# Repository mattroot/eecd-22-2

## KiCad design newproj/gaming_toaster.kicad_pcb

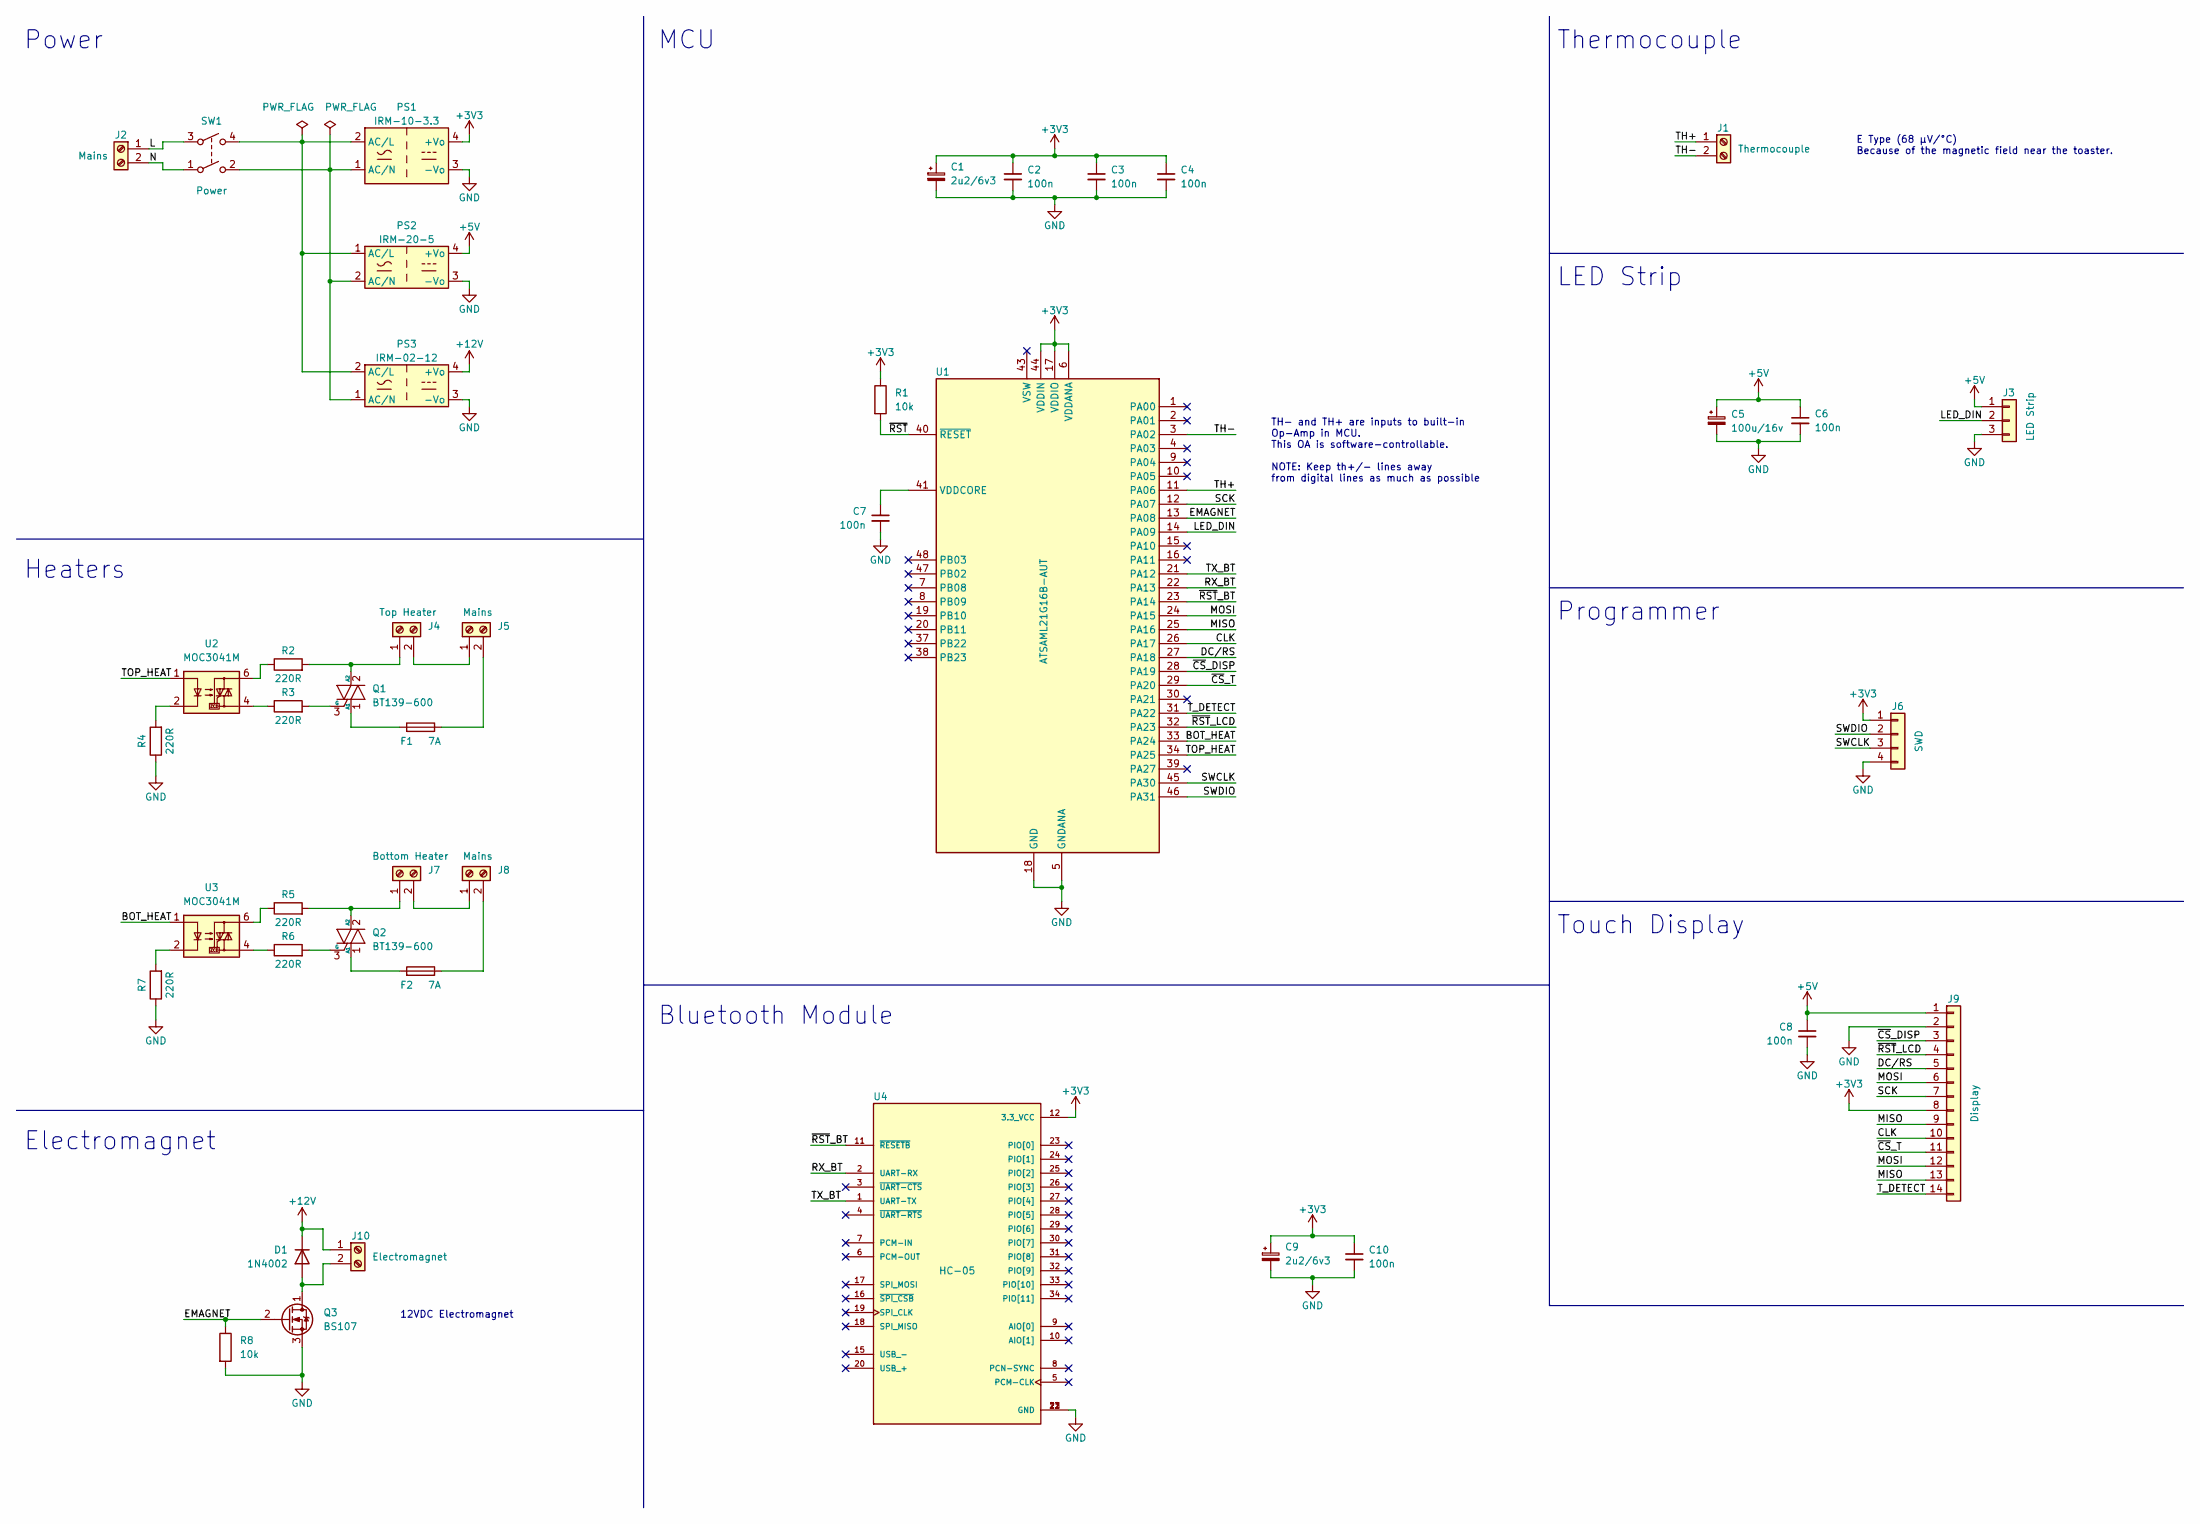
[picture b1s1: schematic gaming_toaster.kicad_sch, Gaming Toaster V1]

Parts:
C1, C9: 2u2/6v3; CP_Elec_4x3
C2, C3, C4, C6, C7, C8, C10: 100n; C_0603_1608Metric
C5: 100u/16v; CP_Elec_6.3x3.9
D1: 1N4002; D_SMA
F1, F2: 7A; Fuseholder_Clip-5x20mm_Littelfuse_520_Inline_P20.50x5.80mm_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
J1: Thermocouple; Molex_Micro-Fit_3.0_43650-0215_1x02_P3.00mm_Vertical
J2, J5, J8: Mains; TerminalBlock_bornier-2_P5.08mm
J3: LED Strip; Molex_Micro-Fit_3.0_43650-0315_1x03_P3.00mm_Vertical
J4: Top Heater; TerminalBlock_bornier-2_P5.08mm
J6: SWD; PinHeader_1x04_P2.54mm_Vertical
J7: Bottom Heater; TerminalBlock_bornier-2_P5.08mm
J9: Display; Molex_SlimStack_502426-1410_2x07_P0.40mm_Vertical
J10: Electromagnet; TerminalBlock_bornier-2_P5.08mm
PS1: IRM-10-3.3; Converter_ACDC_MeanWell_IRM-10-xx_THT
PS2: IRM-20-5; Converter_ACDC_MeanWell_IRM-20-xx_THT
PS3: IRM-02-12; Converter_ACDC_MeanWell_IRM-02-xx_THT
Q1, Q2: BT139-600; TO-220-3_Vertical
Q3: BS107; TO-92_Inline
R1, R8: 10k; R_0603_1608Metric
R2, R3, R4, R5, R6, R7: 220R; R_0603_1608Metric
SW1: Power; SolderWire-0.75sqmm_1x04_P4.8mm_D1.25mm_OD2.3mm
U1: ATSAML21G16B-AUT; TQFP-48_7x7mm_P0.5mm
U2, U3: MOC3041M; DIP-6_W7.62mm
U4: HC-05; PARTREV v1.0

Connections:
+3V3: C1.1, C2.1, C3.1, C4.1, C9.1, C10.1, J6.1, J9.8, PS1.4 (+Vo), R1.1, U1.6 (VDDANA), U1.17 (VDDIO), U1.36 (VDDIO), U1.44 (VDDIN), U4.12 (3.3_VCC)
+5V: C5.1, C6.1, C8.1, J3.1, J9.1, PS2.4 (+Vo)
+12V: D1.1 (K), J10.1, PS3.4 (+Vo)
/BOT_HEAT: U1.33 (PA24), U3.1
/CLK: J9.10, U1.26 (PA17)
/DC/RS: J9.5, U1.27 (PA18)
/EMAGNET: Q3.2 (G), R8.1, U1.13 (PA08)
/L: J2.1, SW1.3
/LED_DIN: J3.2, U1.14 (PA09)
/MISO: J9.9, J9.13, U1.25 (PA16)
/MOSI: J9.6, J9.12, U1.24 (PA15)
/N: J2.2, SW1.1
/RX_BT: U1.22 (PA13), U4.2 (UART-RX)
/SCK: J9.7, U1.12 (PA07)
/SWCLK: J6.3, U1.45 (PA30)
/SWDIO: J6.2, U1.46 (PA31)
/TH+: J1.1, U1.11 (PA06)
/TH-: J1.2, U1.3 (PA02)
/TOP_HEAT: U1.34 (PA25), U2.1
/TX_BT: U1.21 (PA12), U4.1 (UART-TX)
/T_DETECT: J9.14, U1.31 (PA22)
/~CS_DISP: J9.3, U1.28 (PA19)
/~CS_T: J9.11, U1.29 (PA20)
/~RST: R1.2, U1.40 (~RESET)
/~RST_BT: U1.23 (PA14), U4.11 (~RESETB)
/~RST_LCD: J9.4, U1.32 (PA23)
GND: C1.2, C2.2, C3.2, C4.2, C5.2, C6.2, C7.2, C8.2, C9.2, C10.2, J3.3, J6.4, J9.2, PS1.3 (-Vo), PS2.3 (-Vo), PS3.3 (-Vo), Q3.3 (S), R4.1, R7.1, R8.2, U1.5 (GNDANA), U1.18 (GND), U1.35 (GND), U1.42 (GND), U4.13 (GND), U4.21 (GND), U4.22 (GND)
unnamed: PS1.2 (AC/L), PS2.1 (AC/L), PS3.2 (AC/L), SW1.4
unnamed: PS1.1 (AC/N), PS2.2 (AC/N), PS3.1 (AC/N), SW1.2
unnamed: D1.2 (A), J10.2, Q3.1 (D)
unnamed: J4.1, Q1.2 (A2), R2.2
unnamed: J4.2, J5.1
unnamed: F1.1, J5.2
unnamed: J7.1, Q2.2 (A2), R5.2
unnamed: J7.2, J8.1
unnamed: F2.1, J8.2
unnamed: F1.2, Q1.1 (A1)
unnamed: Q1.3 (G), R3.2
unnamed: F2.2, Q2.1 (A1)
unnamed: Q2.3 (G), R6.2
unnamed: R2.1, U2.6
unnamed: R3.1, U2.4
unnamed: R4.2, U2.2
unnamed: R5.1, U3.6
unnamed: R6.1, U3.4
unnamed: R7.2, U3.2
unnamed: C7.1, U1.41 (VDDCORE)

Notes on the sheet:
MCU
Power
Bluetooth Module
E Type (68 µV/°C) Because of the magnetic field near the toaster.
Touch Display
Heaters
12VDC Electromagnet
LED Strip
Electromagnet
Thermocouple
TH- and TH+ are inputs to built-in Op-Amp in MCU. This OA is software-controllable. NOTE: Keep th+/- lines away from digital lines as much as possible
Programmer

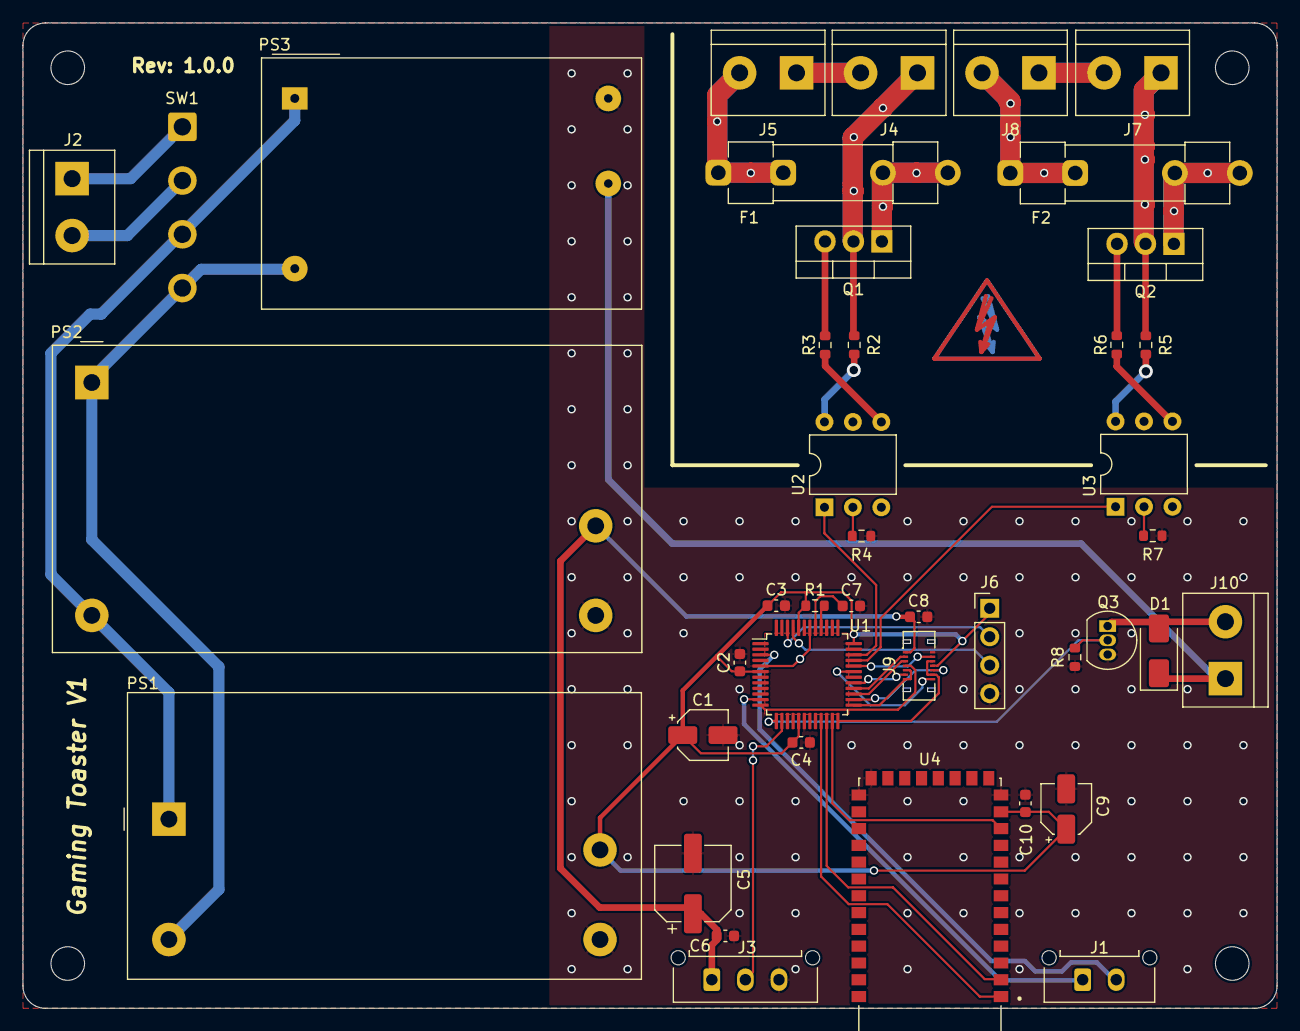
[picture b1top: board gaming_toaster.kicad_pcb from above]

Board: 2 copper layers, 112.0 x 88.0 mm, 42 parts (0 on the bottom side), 47 nets.

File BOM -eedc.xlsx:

# | Element | Q-ty | buying price | buying price | Shop
1 | 4DLCD-24320240-CTP-IPS4D SYSTEMS | 1 | 25.45 [USD/SZT] | 25.45 [USD/50 SZT] | https://www.tme.eu/en/details/4dlcd-24320240-ci/lcd-graphic-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
2 | ESP32­S3­WROOM­2 | 1 | 46.06 [USD/SZT] | 46.06 [USD/50 SZT] | https://www.tme.eu/pl/details/esp32s3-wrm2-16r8v/moduly-iot-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
3 | KAM1505CHINFA ELECTRONICS AC-DC 5v | 1 | 26.5 [USD/SZT] | 26.5 [USD/50 SZT] | https://www.tme.eu/pl/details/ac15w85-265_5/przetwornice-ac-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
4 | AME1-3.3SJZAIMTEC AC-DC 3.3v | 1 | 10.91 [USD/SZT] | 10.91 [USD/50 SZT] | https://www.tme.eu/pl/details/ame1-3.3sjz/przetwornice-ac-dc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
5 | KAM1503 AC - DC POWER MODULE13 ~ 15W UL / cUL / TUV / CE | 1 | 1.8 [USD/SZT] | 1.8 [USD/50 SZT] | https://www.compel.ru/infosheet/CHINFA/KAM1503
6 | ZIF0540DH-CF25RIVERDI | 1 | 1.6 [USD/SZT] | 1.6 [USD/50 SZT] | https://www.tme.eu/en/details/zif0540dh-cf25/displays-access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
7 | WS2812BWORLDSEMI | 1 | 0.4 [USD/SZT] | 0.4 [USD/50 SZT] | https://www.tme.eu/pl/details/ws2812b/diody-led-smd-kolorowe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
8 | H8553VBBG3076WBULGIN | 1 | 4.51 [USD/SZT] | 4.51 [USD/50 SZT] | https://www.tme.eu/pl/details/ae-h8553vbnac/przelaczniki-typ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
9
10 | IRM-20-5 - Mean Well Web | 1 | 12.27 [USD/SZT] | 11.98 [USD/50 SZT] | https://www.meanwell-web.com/en-gb/ac-dc-single-output-encap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
11 | Kondensator elektrolityczny SMD 10UF 16V | 3 | 0.09 [USD/SZT] | 0.03 [USD/50 SZT] | https://www.trim-pot.com.pl/pl/p/Kondensator-elektrolityczny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
12 | Philips Cc 2U2 6V3 | 6 | 0.38 [USD/SZT] | 0.26 [USD/50 SZT] | https://nowyelektronik.pl/index.php?id_product=28116&control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
13 | ATSAML21G16B-AUT | 1 | 4.43 [USD/SZT] | 3.98 [USD/50 SZT] | https://www.mouser.pl/ProductDetail/Microchip-Technology/ATS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
14 | PinHeader 1x04 P 2.54mm_Vertical | 1 | 0.87 [USD/SZT] | 0.59 [USD/50 SZT] | https://www.mouser.pl/ProductDetail/Mill-Max/310-47-105-41-0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
15 | R_0603_1608 Metric 220R | 6 | 3.00 [USD/SZT] | 2.14 [USD/50 SZT] | https://www.mouser.pl/c/passive-components/resistors/smd-res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
16 | R_0603_1608 Metric 100n | 9 | 3.00 [USD/SZT] | 2.14 [USD/50 SZT] | https://www.mouser.pl/c/passive-components/resistors/smd-res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
17 | 691214110002S | 1 | 1.20 [USD/SZT] | 1.10 [USD/50 SZT] | https://www.mouser.pl/ProductDetail/Wurth-Elektronik/6912141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
18 | PTS645SL50-2 LFSC&K | 1 | 0.23 [USD/SZT] | 0.19[USD/50 SZT] | https://www.tme.eu/pl/details/pts645sl50-2/mikroprzelaczniki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
19 | MOC3041M | 2 | 1.11 [USD/SZT] | 0.48[USD/50 SZT] | https://www.mouser.pl/ProductDetail/onsemi-Fairchild/MOC3041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
20 | Littelfuse 05200001N | 2 | 0.30 [USD/SZT] | 0.27[USD/50 SZT] | https://us.rs-online.com/product/littelfuse/05200001n/70519399/
21 | BS107 MOS-N-FET 200V 0.15A 0.8W TO92 | 1 | 0.65 [USD/SZT] | 0.58[USD/50 SZT] | https://www.sklep.cyfronika.com.pl/pl/p/BS107-Tranzystor-MOS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
22 | BLUETOOTH HC-05 AVR ARM ARDUINO | 1 | 6.33 [USD/SZT] | 6.11[USD/50 SZT] | https://modulosy.pl/moduly-radiowe/105-modul-bluetooth-hc-05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
23 | PWR-SWITCH 230V 16A | 1 | 8.13 [USD/SZT] | 7.82[USD/50 SZT] | https://www.olimex.com/Products/Duino/Shields/PWR-SWITCH/
24 | MAX6675 Thermocouple | 1 | 5.86 [USD/SZT] | 5.62[USD/50 SZT] | https://sklep.avt.pl/modul-max6675-miernik-temperatury-do-te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
25 | R_0603_1608 Metric 10k | 2 | 3.00 [USD/SZT] | 2.14 [USD/50 SZT] | https://www.mouser.pl/c/passive-components/resistors/smd-res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
26 | BT139-600E 600V/16A - THT - 5szt. | 2 | 3.31 [USD/SZT] | 3.14 [USD/50 SZT] | https://botland.com.pl/triaki/1280-triak-bt139-600e-600v16a-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
27 | 1776275-2TE CONNECTIVITY | 1 | 0.52 [USD/SZT] | 0.43 [USD/50 SZT] | https://www.tme.eu/pl/details/1776275-2/listwy-zaciskowe-do-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
28 | 436450200 MOLEX | 1 | 0.92 [USD/SZT] | 0.37 [USD/50 SZT] | https://www.tme.eu/pl/details/mx-43645-0200/zlacza-sygnalowe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
29 | M20-7820446 | 1 | 1.03 [USD/SZT] | 0.83 [USD/50 SZT] | https://www.mouser.pl/ProductDetail/Harwin/M20-7820446?qs=vF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
30 | Terminal block Connector 2pin | 1 | 0.58 [USD/SZT] | 0.47 [USD/50 SZT] | https://eshop.sectron.pl/pl/terminal-block-connector-2pin/p-1404/
31 | IRM-02-12 MEAN WELL | 1 | 7.01 [USD/SZT] | 6.15 [USD/50 SZT] | https://www.tme.eu/pl/details/irm-02-12/zasilacze-do-wbudowa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
32 | 1N4002-DIODES | 1 | 0.17 [USD/SZT] | 0.11 [USD/50 SZT] | https://www.mouser.pl/ProductDetail/Diodes-Incorporated/1N40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
33 | 1776275-2TE CONNECTIVITY | 1 | 0.52 [USD/SZT] | 0.43 [USD/50 SZT] | https://www.tme.eu/pl/details/1776275-2/listwy-zaciskowe-do-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
34 | 709-IRM10-3.3 MEAN WELL | 1 | 11.12 [USD/SZT] | 10.12 [USD/50 SZT] | https://www.mouser.pl/ProductDetail/MEAN-WELL/IRM-10-3.3?qs=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

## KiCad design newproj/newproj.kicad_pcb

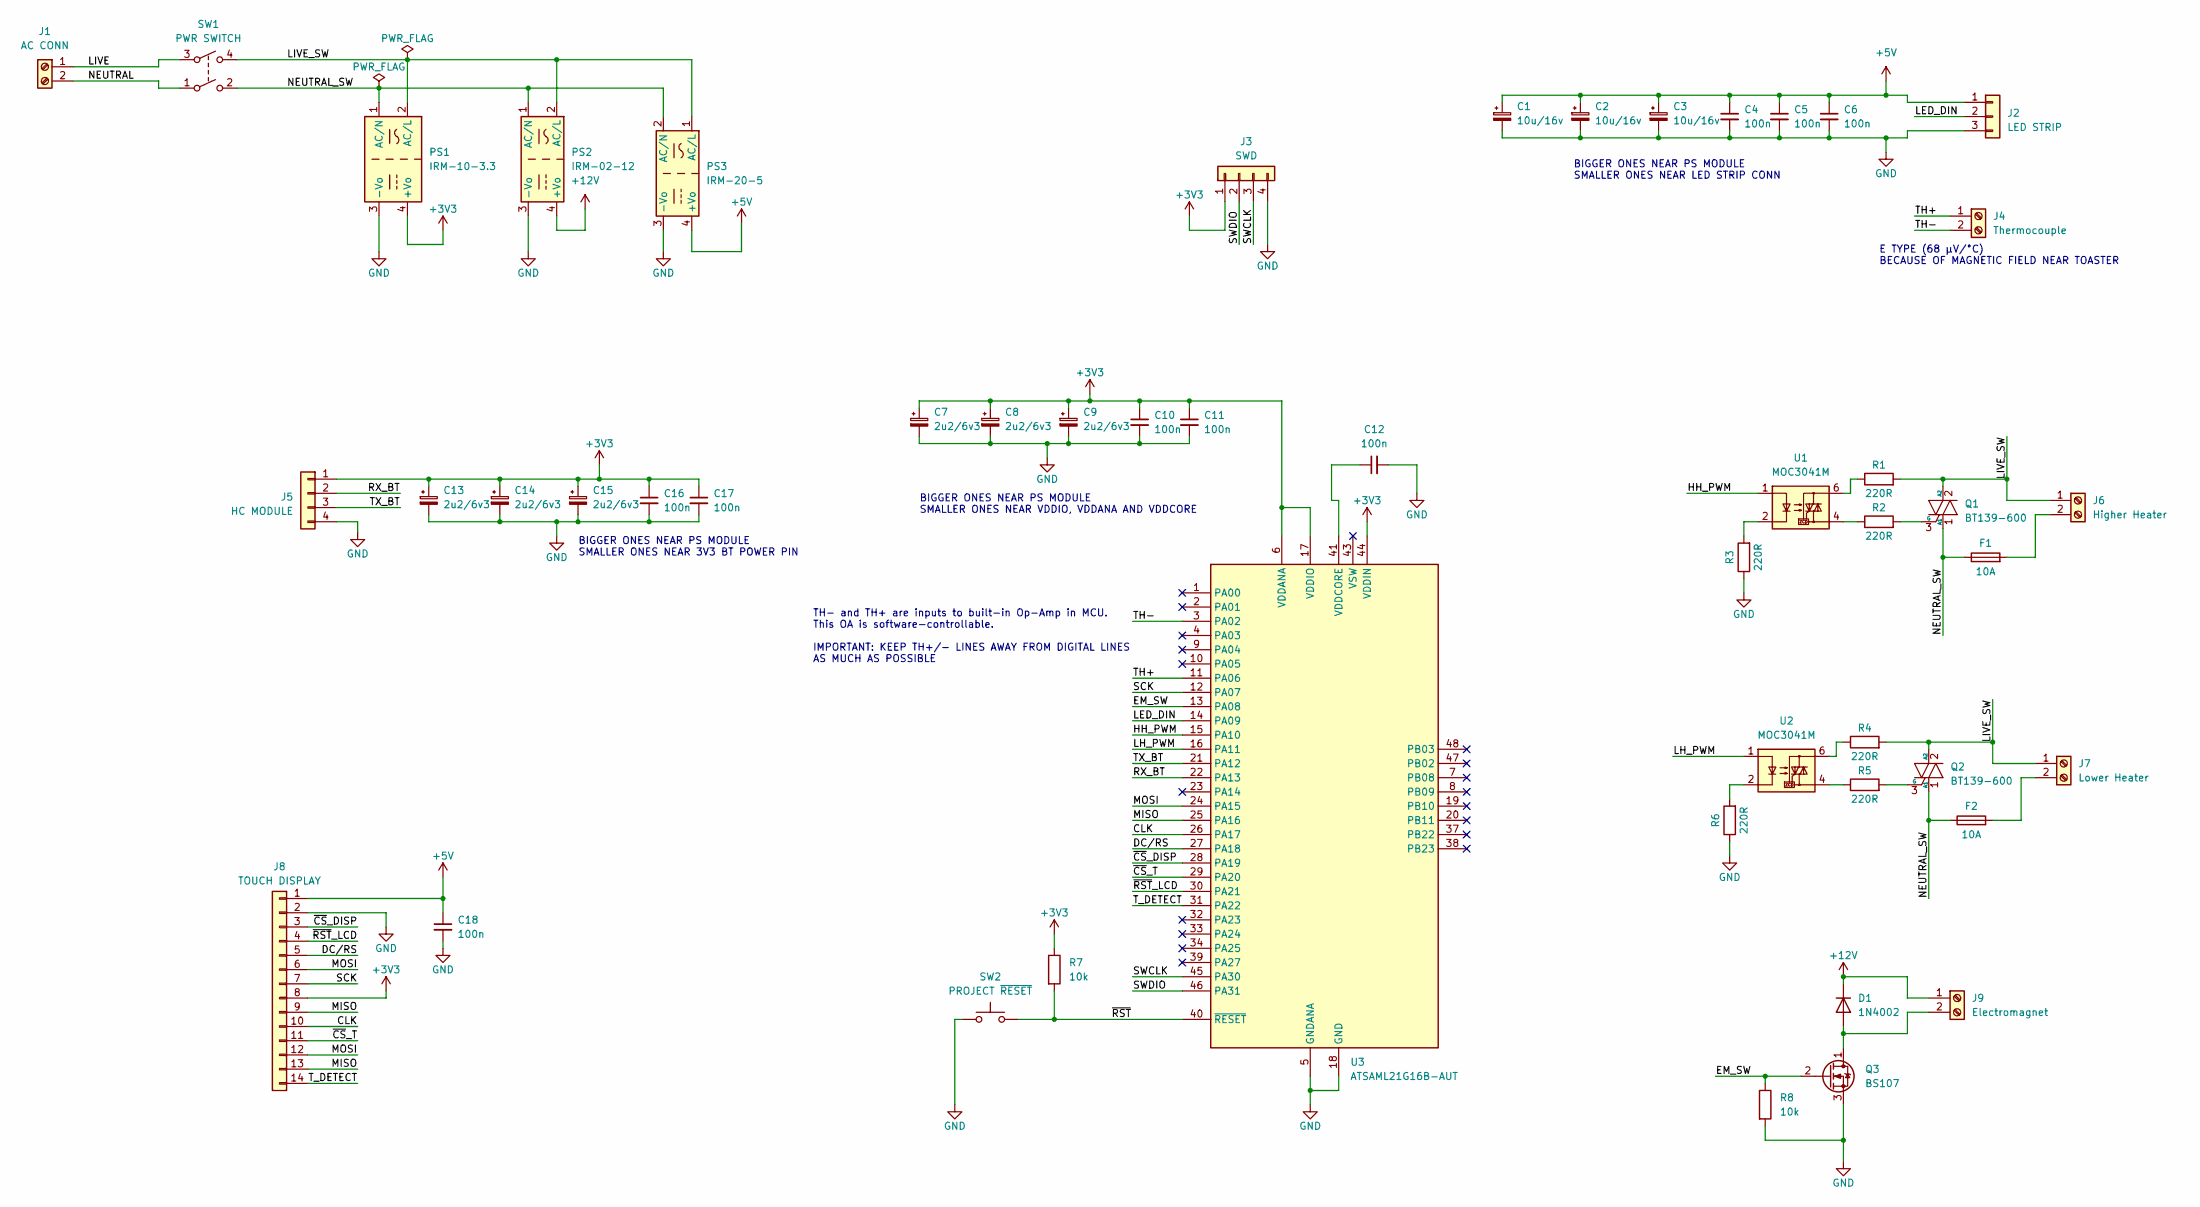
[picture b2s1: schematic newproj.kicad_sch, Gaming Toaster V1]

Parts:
C1, C2, C3: 10u/16v; CP_Elec_6.3x3.9
C4, C5, C6, C10, C11, C12, C16, C17, C18: 100n; C_0603_1608Metric
C7, C8, C9, C13, C14, C15: 2u2/6v3; CP_Elec_4x3
D1: 1N4002; D_SMA
F1, F2: 10A; Fuseholder_Clip-5x20mm_Littelfuse_520_Inline_P20.50x5.80mm_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
J1: AC CONN; TerminalBlock_bornier-2_P5.08mm
J2: LED STRIP; Molex_Micro-Fit_3.0_43650-0315_1x03_P3.00mm_Vertical
J3: SWD; PinHeader_1x04_P2.54mm_Vertical
J4: Thermocouple; TerminalBlock_bornier-2_P5.08mm
J5: HC MODULE; PinHeader_1x04_P2.54mm_Vertical
J6: Higher Heater; TerminalBlock_bornier-2_P5.08mm
J7: Lower Heater; TerminalBlock_bornier-2_P5.08mm
J8: TOUCH DISPLAY; PinHeader_1x14_P2.54mm_Vertical
J9: Electromagnet; TerminalBlock_bornier-2_P5.08mm
PS1: IRM-10-3.3; Converter_ACDC_MeanWell_IRM-10-xx_THT
PS2: IRM-02-12; Converter_ACDC_MeanWell_IRM-02-xx_THT
PS3: IRM-20-5; Converter_ACDC_MeanWell_IRM-20-xx_THT
Q1, Q2: BT139-600; TO-220-3_Vertical
Q3: BS107; TO-92_Inline
R1, R2, R3, R4, R5, R6: 220R; R_0603_1608Metric
R7, R8: 10k; R_0603_1608Metric
SW1: PWR SWITCH; PinHeader_1x04_P2.54mm_Vertical
SW2: PROJECT ~{RESET}; SW_SPST_PTS645
U1, U2: MOC3041M; DIP-6_W7.62mm
U3: ATSAML21G16B-AUT; TQFP-48_7x7mm_P0.5mm

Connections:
+3V3: C7.1, C8.1, C9.1, C10.1, C11.1, C13.1, C14.1, C15.1, C16.1, C17.1, J3.1, J5.1, J8.8, PS1.4 (+Vo), R7.1, U3.6 (VDDANA), U3.17 (VDDIO), U3.36 (VDDIO), U3.44 (VDDIN)
+5V: C1.1, C2.1, C3.1, C4.1, C5.1, C6.1, C18.1, J2.1, J8.1, PS3.4 (+Vo)
+12V: D1.1 (K), J9.1, PS2.4 (+Vo)
/CLK: J8.10, U3.26 (PA17)
/DC/RS: J8.5, U3.27 (PA18)
/EM_SW: Q3.2 (G), R8.1, U3.13 (PA08)
/HH_PWM: U1.1, U3.15 (PA10)
/LED_DIN: J2.2, U3.14 (PA09)
/LH_PWM: U2.1, U3.16 (PA11)
/LIVE: J1.1, SW1.3
/LIVE_SW: J6.1, J7.1, PS1.2 (AC/L), PS2.2 (AC/L), PS3.1 (AC/L), Q1.2 (A2), Q2.2 (A2), R1.2, R4.2, SW1.4
/MISO: J8.9, J8.13, U3.25 (PA16)
/MOSI: J8.6, J8.12, U3.24 (PA15)
/NEUTRAL: J1.2, SW1.1
/NEUTRAL_SW: F1.1, F2.1, PS1.1 (AC/N), PS2.1 (AC/N), PS3.2 (AC/N), Q1.1 (A1), Q2.1 (A1), SW1.2
/RX_BT: J5.2, U3.22 (PA13)
/SCK: J8.7, U3.12 (PA07)
/SWCLK: J3.3, U3.45 (PA30)
/SWDIO: J3.2, U3.46 (PA31)
/TH+: J4.1, U3.11 (PA06)
/TH-: J4.2, U3.3 (PA02)
/TX_BT: J5.3, U3.21 (PA12)
/T_DETECT: J8.14, U3.31 (PA22)
/~CS_DISP: J8.3, U3.28 (PA19)
/~CS_T: J8.11, U3.29 (PA20)
/~RST: R7.2, SW2.2, U3.40 (~RESET)
/~RST_LCD: J8.4, U3.30 (PA21)
GND: C1.2, C2.2, C3.2, C4.2, C5.2, C6.2, C7.2, C8.2, C9.2, C10.2, C11.2, C12.2, C13.2, C14.2, C15.2, C16.2, C17.2, C18.2, J2.3, J3.4, J5.4, J8.2, PS1.3 (-Vo), PS2.3 (-Vo), PS3.3 (-Vo), Q3.3 (S), R3.1, R6.1, R8.2, SW2.1, U3.5 (GNDANA), U3.18 (GND), U3.35 (GND), U3.42 (GND)
unnamed: D1.2 (A), J9.2, Q3.1 (D)
unnamed: F1.2, J6.2
unnamed: F2.2, J7.2
unnamed: Q1.3 (G), R2.2
unnamed: Q2.3 (G), R5.2
unnamed: R1.1, U1.6
unnamed: R2.1, U1.4
unnamed: R3.2, U1.2
unnamed: R4.1, U2.6
unnamed: R5.1, U2.4
unnamed: R6.2, U2.2
unnamed: C12.1, U3.41 (VDDCORE)

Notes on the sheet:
E TYPE (68 µV/°C) BECAUSE OF MAGNETIC FIELD NEAR TOASTER
BIGGER ONES NEAR PS MODULE SMALLER ONES NEAR VDDIO, VDDANA AND VDDCORE
BIGGER ONES NEAR PS MODULE SMALLER ONES NEAR 3V3 BT POWER PIN
TH- and TH+ are inputs to built-in Op-Amp in MCU. This OA is software-controllable. IMPORTANT: KEEP TH+/- LINES AWAY FROM DIGITAL LINES AS MUCH AS POSSIBLE
BIGGER ONES NEAR PS MODULE SMALLER ONES NEAR LED STRIP CONN

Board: 2 copper layers, 49 parts (0 on the bottom side), 40 nets, no tracks yet.

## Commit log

2023-01-10 Create LICENSE
2023-01-24 Add display connector and change it in parts.txt
2023-01-25 Commit several war crimes
2023-01-26 discord is a fuck
2023-02-16 schematic + readying for pcb
2023-02-16 pcb layout draft
